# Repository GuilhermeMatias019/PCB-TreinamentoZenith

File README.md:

# PCB-TreinamentoZenith

## Descrição do Projeto
<p align="center">Este é um projeto de uma placa de circuito impresso(PCB) para desenvolvimento e testes utilizando o microcontrolador STM32F103C8T6 utilizando o software KiCad 6.0.</p>

<a href="https://github.com/GuilhermeMatias019/PCB-TreinamentoZenith#-Perifericos-"><h2> Periféricos </h2></a>

-MPU6050 
-BMP280 
-LED RGB
-2 botões
-LDR
-Relé

-Botão de reset
-Conector micro USB
-Conector para Seial Wire Debug (SWD)
-Conector para seleção do modo de boot
-16 pinos de GPIO disponíveis

Configuração dos pinos do microcontrolador no STM32CubeMX.

<a href="https://github.com/GuilhermeMatias019/PCB-TreinamentoZenith#-Layout-"><h2> Layout </h2></a>

Vista do layout da PCB.

Vista das trilhas na parte de cima da PCB.

Vista das trilhas na parte de baixo da PCB.

<a href="https://github.com/GuilhermeMatias019/PCB-TreinamentoZenith#-3D-"><h2> Vista 3D </h2></a>

Vista 3D da parte de cima da PCB.

Vista 3D da parte de baixo da PCB.

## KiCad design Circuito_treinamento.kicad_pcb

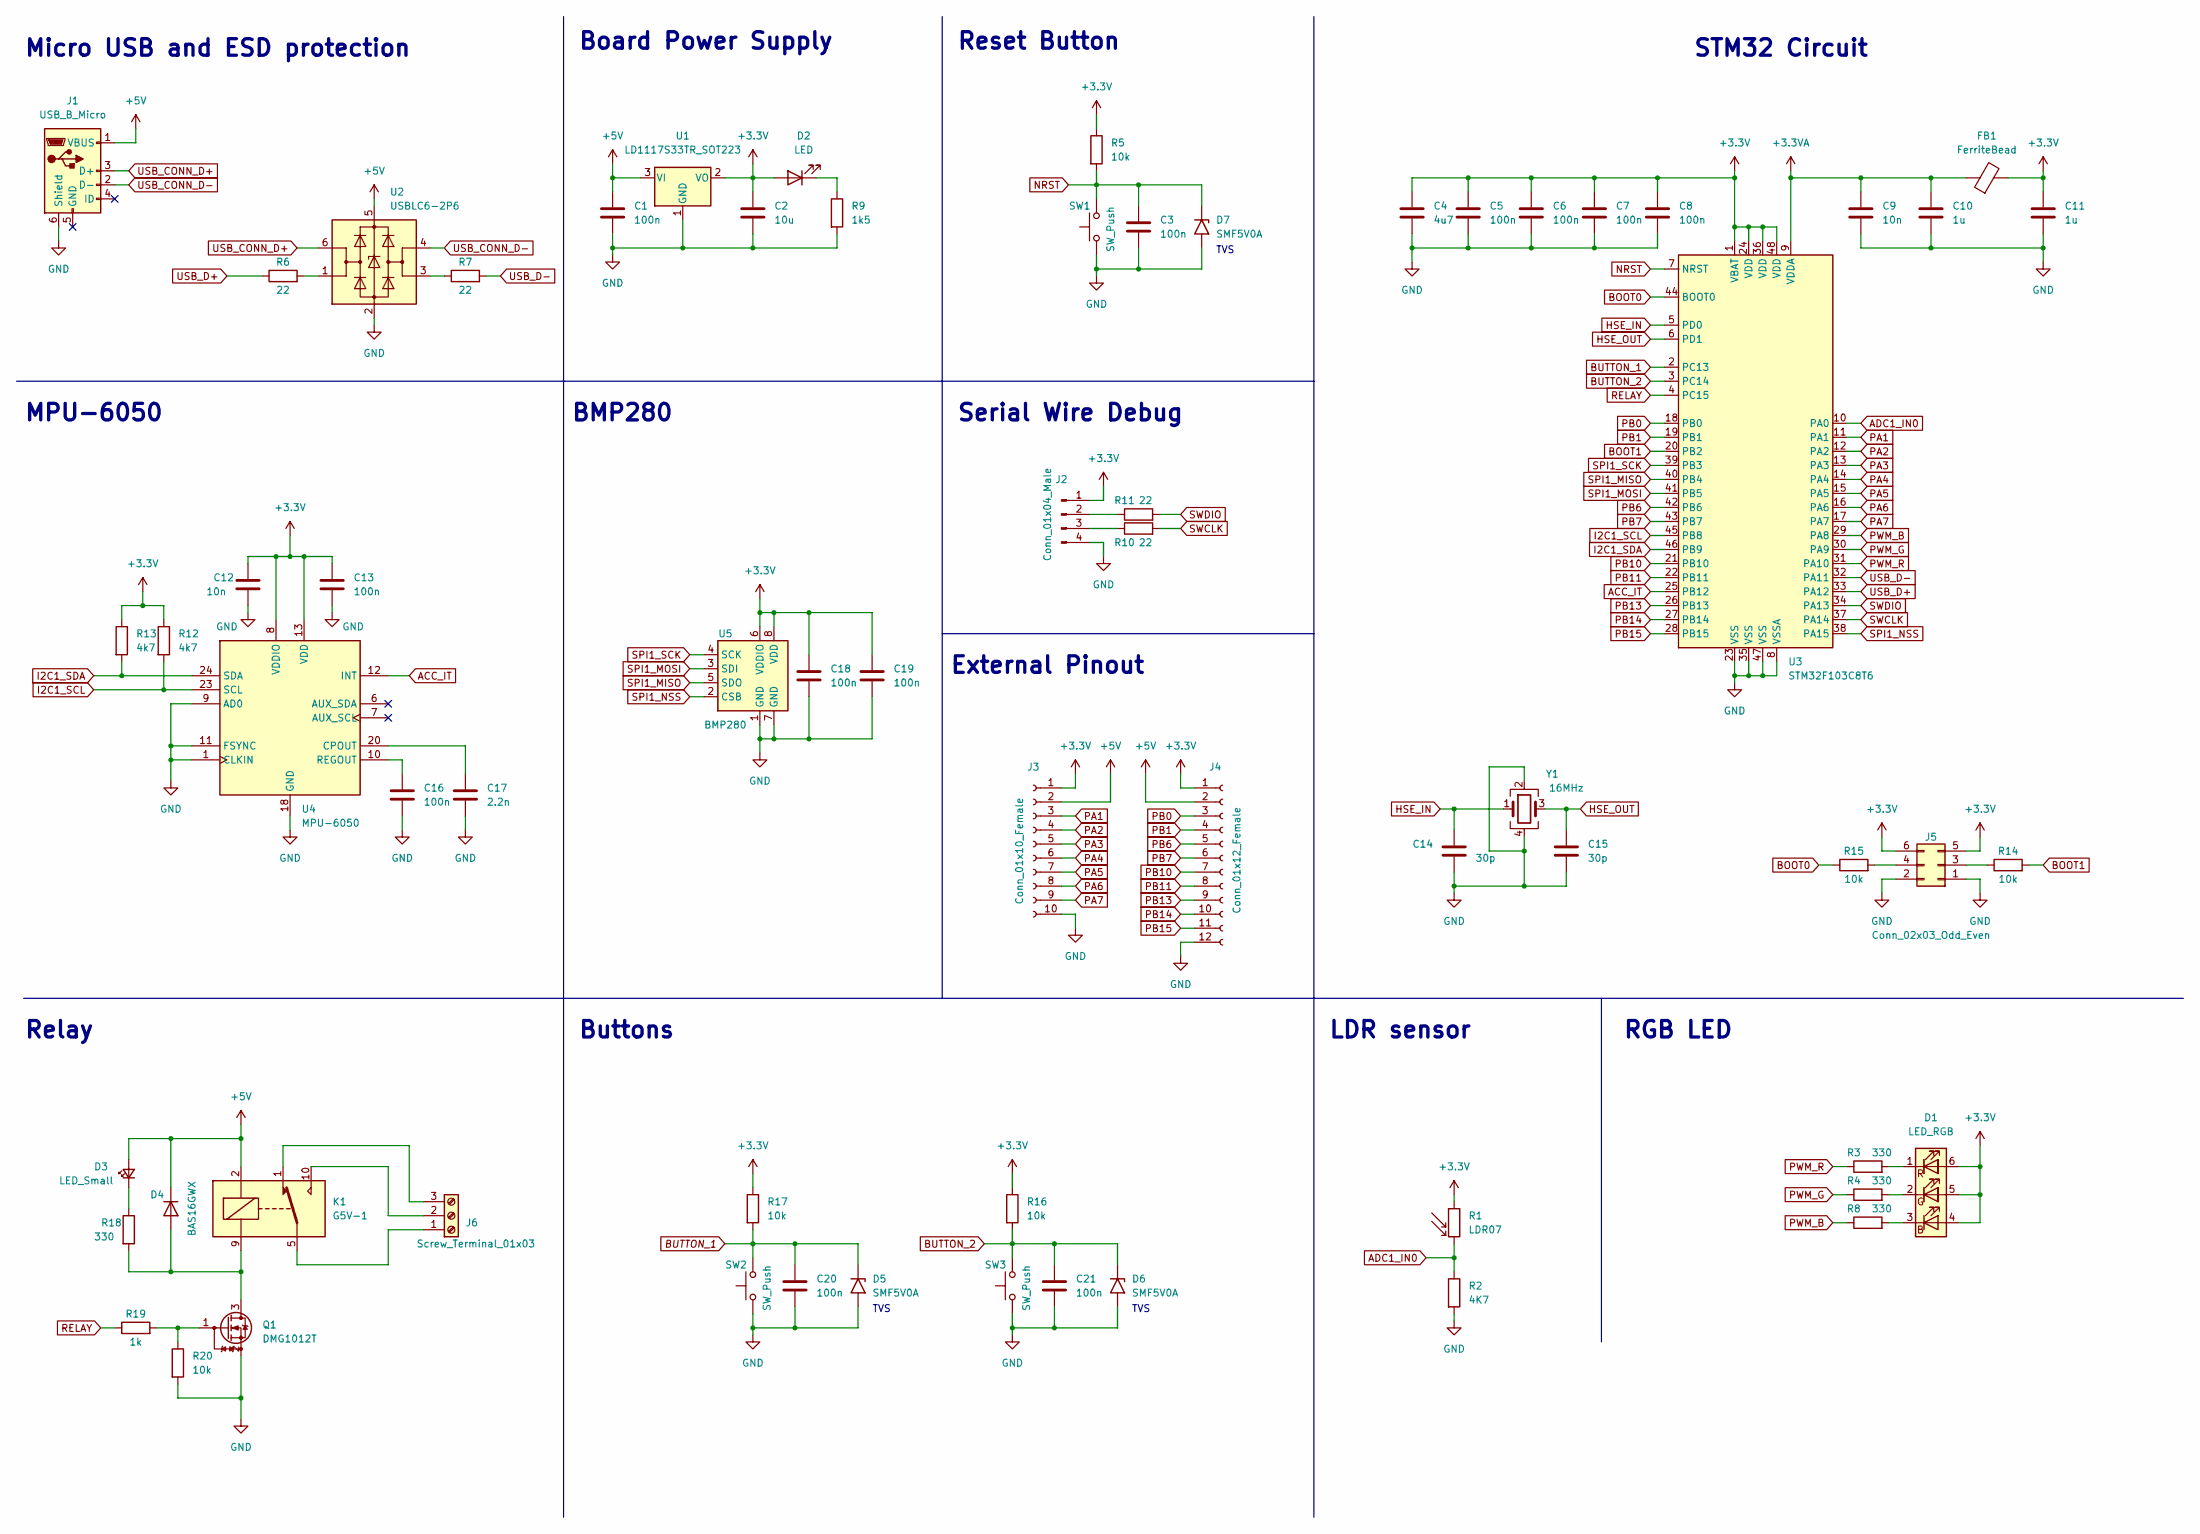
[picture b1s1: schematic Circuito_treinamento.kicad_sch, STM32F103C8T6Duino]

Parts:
C1, C3, C16, C18, C19, C20, C21: 100n; C_0805_2012Metric
C2: 10u; C_0805_2012Metric
C4: 4u7; C_0805_2012Metric
C5, C6, C7, C8, C13: 100n; C_0603_1608Metric
C9, C12: 10n; C_0603_1608Metric
C10, C11: 1u; C_0805_2012Metric
C14, C15: 30p; C_0805_2012Metric
C17: 2.2n; C_0805_2012Metric
D1: LED_RGB; LED_RGB_5050-6
D2: LED; LED_0603_1608Metric
D3: LED_Small; LED_0603_1608Metric
D4: BAS16GWX; D_SOD-323F
D5, D6, D7: SMF5V0A; D_SMF
FB1: FerriteBead; L_0603_1608Metric
J1: USB_B_Micro; USB_Micro-B_Molex_47346-0001
J2: Conn_01x04_Male; PinHeader_1x04_P2.54mm_Vertical
J3: Conn_01x10_Female; PinSocket_1x10_P2.54mm_Vertical
J4: Conn_01x12_Female; PinSocket_1x12_P2.54mm_Vertical
J5: Conn_02x03_Odd_Even; PinHeader_2x03_P1.00mm_Vertical
J6: Screw_Terminal_01x03; TerminalBlock_4Ucon_1x03_P3.50mm_Vertical
K1: G5V-1; Relay_SPDT_Omron_G5V-1
Q1: DMG1012T; SOT-523
R1: LDR07; R_LDR_5.1x4.3mm_P3.4mm_Vertical
R2: 4K7; R_0805_2012Metric
R3, R4, R8, R18: 330; R_0805_2012Metric
R5, R14, R15, R16, R17, R20: 10k; R_0805_2012Metric
R6, R7, R10, R11: 22; R_0805_2012Metric
R9: 1k5; R_0805_2012Metric
R12, R13: 4k7; R_0805_2012Metric
R19: 1k; R_0805_2012Metric
SW1, SW2, SW3: SW_Push; SW_Push_1P1T_NO_6x6mm_H9.5mm
U1: LD1117S33TR_SOT223; SOT-223-3_TabPin2
U2: USBLC6-2P6; SOT-666
U3: STM32F103C8T6; LQFP-48_7x7mm_P0.5mm
U4: MPU-6050; InvenSense_QFN-24_4x4mm_P0.5mm
U5: BMP280; Bosch_LGA-8_2x2.5mm_P0.65mm_ClockwisePinNumbering
Y1: 16MHz; Crystal_SMD_3225-4Pin_3.2x2.5mm

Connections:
+3.3V: C2.1, C4.1, C5.1, C6.1, C7.1, C8.1, C11.1, C12.1, C13.1, C18.1, C19.1, D1.4 (BA), D1.5 (GA), D1.6 (RA), D2.2 (A), FB1.2, J2.1, J3.1, J4.1, J5.5, J5.6, R1.1, R5.1, R12.1, R13.1, R16.1, R17.1, U1.2 (VO), U3.1 (VBAT), U3.24 (VDD), U3.36 (VDD), U3.48 (VDD), U4.8 (VDDIO), U4.13 (VDD), U5.6 (VDDIO), U5.8 (VDD)
+3.3VA: C9.1, C10.1, FB1.1, U3.9 (VDDA)
+5V: C1.1, D3.2 (A), D4.1 (K), J1.1 (VBUS), J3.2, J4.2, K1.2, U1.3 (VI), U2.5 (VBUS)
ACC_IT: U3.25 (PB12), U4.12 (INT)
ADC1_IN0: R1.2, R2.1, U3.10 (PA0)
BOOT0: R15.1, U3.44 (BOOT0)
BOOT1: R14.2, U3.20 (PB2)
BUTTON_1: C20.1, D5.1 (A1), R17.2, SW2.2, U3.2 (PC13)
BUTTON_2: C21.1, D6.1 (A1), R16.2, SW3.2, U3.3 (PC14)
GND: C1.2, C2.2, C3.2, C4.2, C5.2, C6.2, C7.2, C8.2, C9.2, C10.2, C11.2, C12.2, C13.2, C14.2, C15.2, C16.2, C17.2, C18.2, C19.2, C20.2, C21.2, D5.2 (A2), D6.2 (A2), D7.2 (A2), J1.6 (Shield), J2.4, J3.10, J4.12, J5.1, J5.2, Q1.2 (S), R2.2, R9.2, R20.2, SW1.1, SW2.1, SW3.1, U1.1 (GND), U2.2 (GND), U3.8 (VSSA), U3.23 (VSS), U3.35 (VSS), U3.47 (VSS), U4.1 (CLKIN), U4.9 (AD0), U4.11 (FSYNC), U4.18 (GND), U5.1 (GND), U5.7 (GND), Y1.2, Y1.4
HSE_IN: C14.1, U3.5 (PD0), Y1.1
HSE_OUT: C15.1, U3.6 (PD1), Y1.3
I2C1_SCL: R12.2, U3.45 (PB8), U4.23 (SCL)
I2C1_SDA: R13.2, U3.46 (PB9), U4.24 (SDA)
NRST: C3.1, D7.1 (A1), R5.2, SW1.2, U3.7 (NRST)
unnamed: C16.1, U4.10 (REGOUT)
unnamed: C17.1, U4.20 (CPOUT)
unnamed: D1.1 (RK), R3.2
unnamed: D1.2 (GK), R4.2
unnamed: D1.3 (BK), R8.2
unnamed: D2.1 (K), R9.1
unnamed: D3.1 (K), R18.1
unnamed: D4.2 (A), K1.9, Q1.3 (D), R18.2
unnamed: J2.2, R11.1
unnamed: J2.3, R10.1
unnamed: J5.3, R14.1
unnamed: J5.4, R15.2
unnamed: J6.1, K1.5, K1.6
unnamed: J6.2, K1.10
unnamed: J6.3, K1.1
unnamed: Q1.1 (G), R19.2, R20.1
unnamed: R6.2, U2.1 (I/O1)
unnamed: R7.1, U2.3 (I/O2)
PA1: J3.3, U3.11 (PA1)
PA2: J3.4, U3.12 (PA2)
PA3: J3.5, U3.13 (PA3)
PA4: J3.6, U3.14 (PA4)
PA5: J3.7, U3.15 (PA5)
PA6: J3.8, U3.16 (PA6)
PA7: J3.9, U3.17 (PA7)
PB0: J4.3, U3.18 (PB0)
PB1: J4.4, U3.19 (PB1)
PB6: J4.5, U3.42 (PB6)
PB7: J4.6, U3.43 (PB7)
PB10: J4.7, U3.21 (PB10)
PB11: J4.8, U3.22 (PB11)
PB13: J4.9, U3.26 (PB13)
PB14: J4.10, U3.27 (PB14)
PB15: J4.11, U3.28 (PB15)
PWM_B: R8.1, U3.29 (PA8)
PWM_G: R4.1, U3.30 (PA9)
PWM_R: R3.1, U3.31 (PA10)
RELAY: R19.1, U3.4 (PC15)
SPI1_MISO: U3.40 (PB4), U5.5 (SDO)
SPI1_MOSI: U3.41 (PB5), U5.3 (SDI)
SPI1_NSS: U3.38 (PA15), U5.2 (CSB)
SPI1_SCK: U3.39 (PB3), U5.4 (SCK)
SWCLK: R10.2, U3.37 (PA14)
SWDIO: R11.2, U3.34 (PA13)
USB_CONN_D+: J1.3 (D+), U2.6 (I/O1)
USB_CONN_D-: J1.2 (D-), U2.4 (I/O2)
USB_D+: R6.1, U3.33 (PA12)
USB_D-: R7.2, U3.32 (PA11)

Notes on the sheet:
TVS
Board Power Supply
Buttons
RGB LED
Relay
LDR sensor
BMP280
MPU-6050
STM32 Circuit
Reset Button
Micro USB and ESD protection
Serial Wire Debug
External Pinout

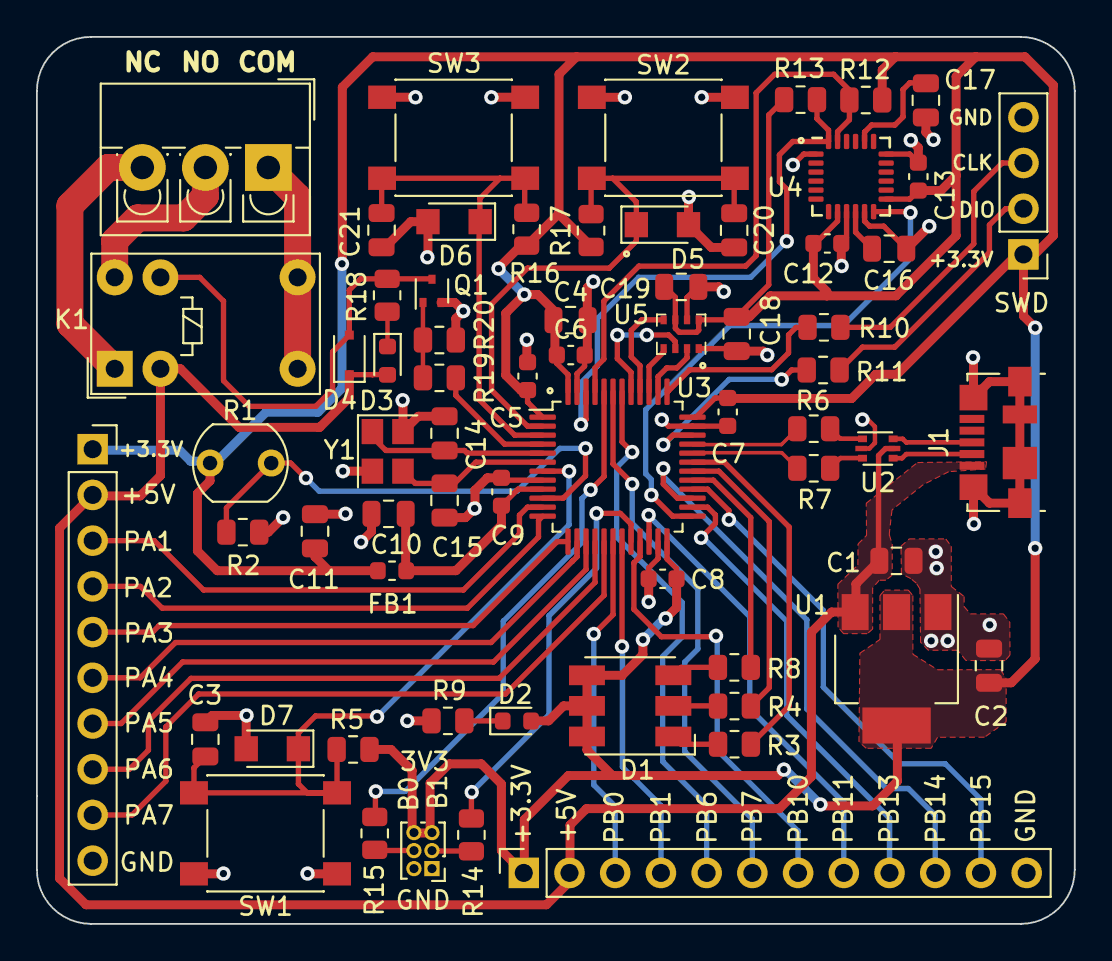
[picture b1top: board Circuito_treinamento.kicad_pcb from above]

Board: 2 copper layers, 57.7 x 49.3 mm, 66 parts (0 on the bottom side), 63 nets.

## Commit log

2024-03-18 primeiro commit
